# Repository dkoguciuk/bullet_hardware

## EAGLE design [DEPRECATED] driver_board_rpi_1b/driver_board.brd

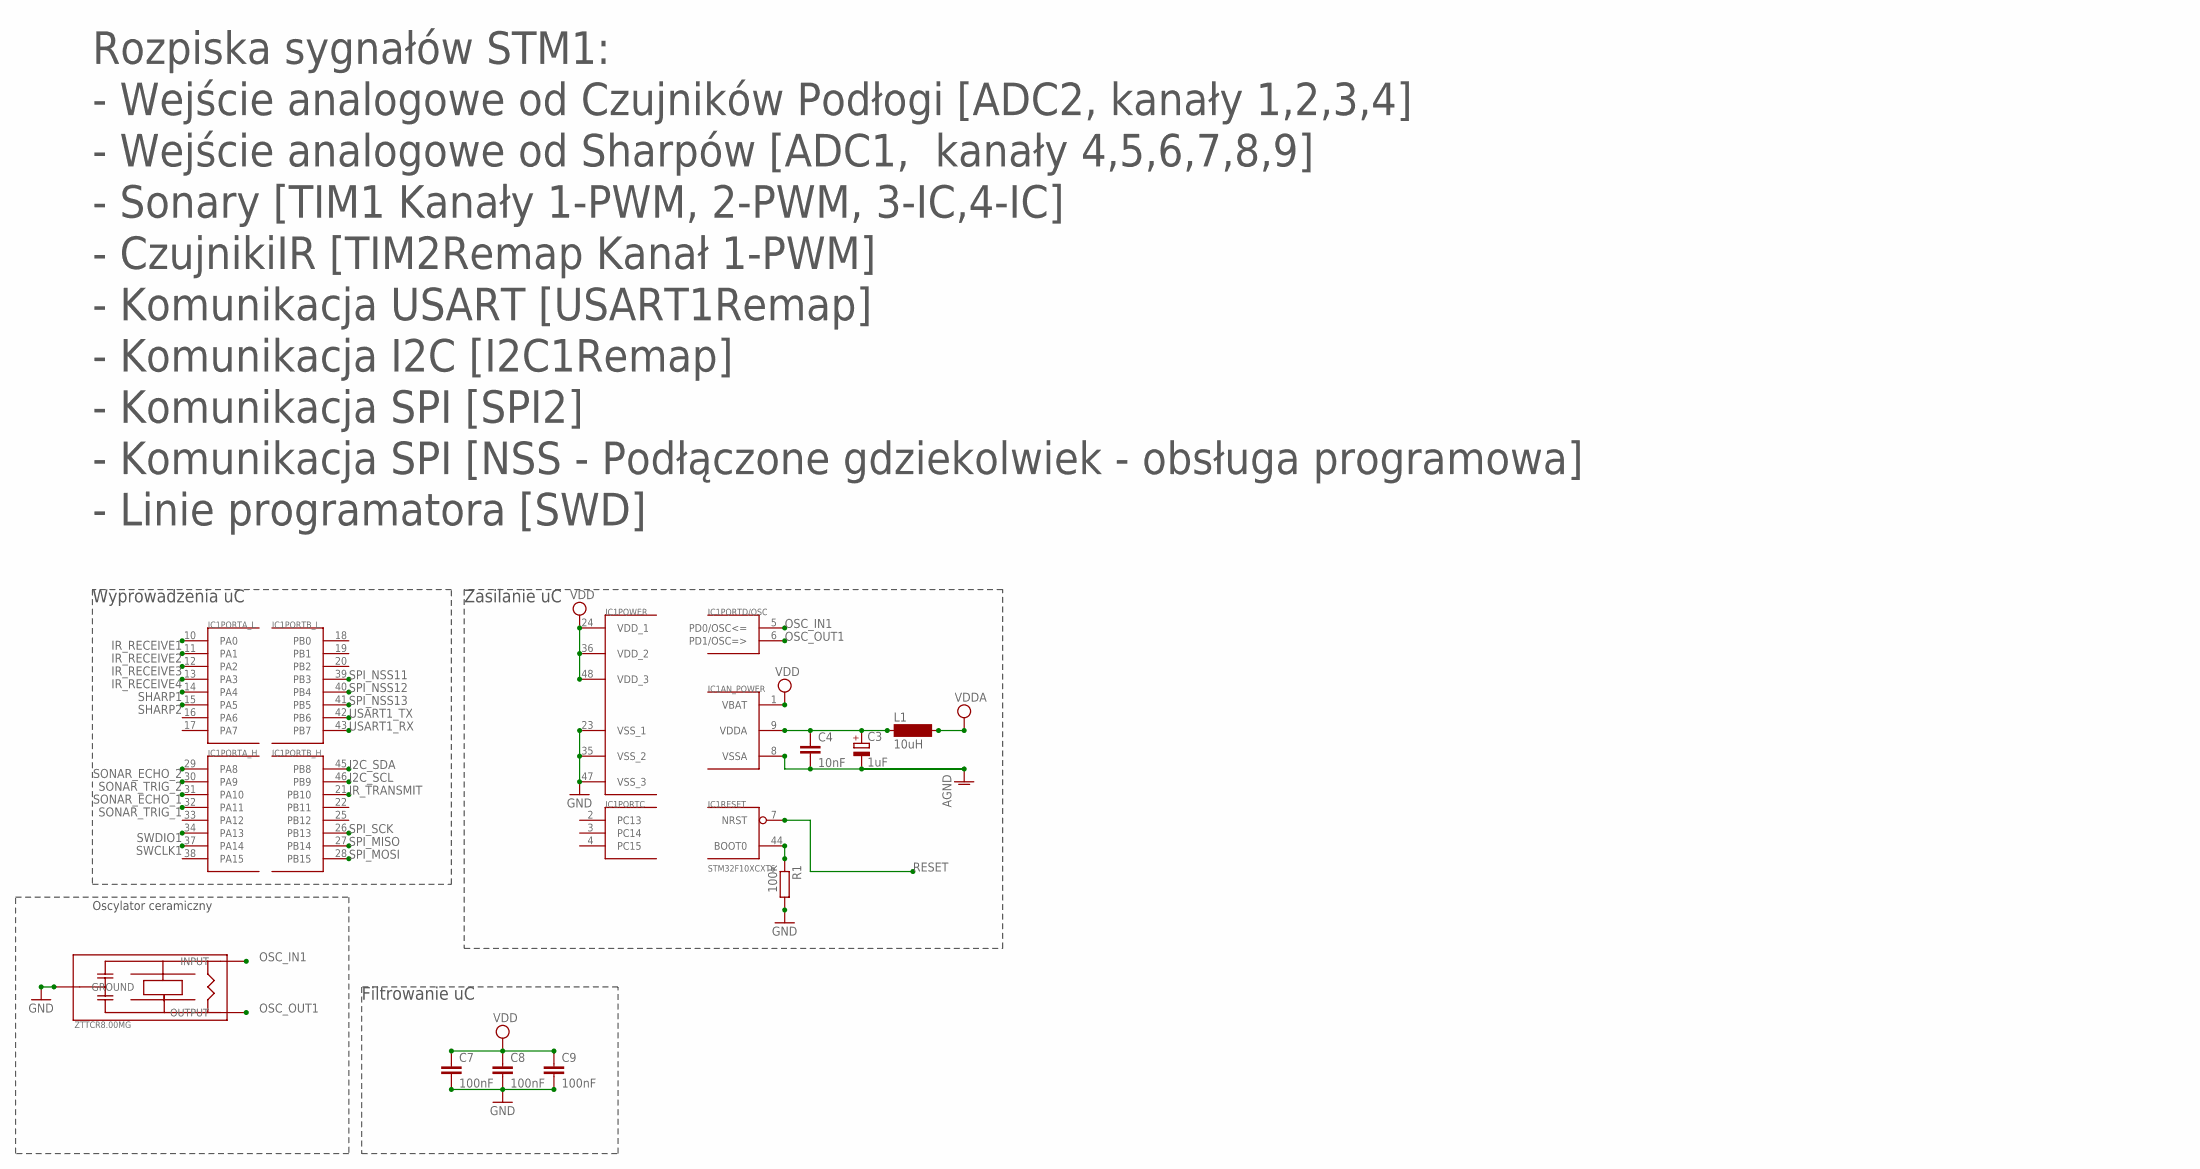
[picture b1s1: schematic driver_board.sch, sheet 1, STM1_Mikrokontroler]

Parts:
C3: 1uF; SMC_A
C4: 10nF; C0805
C7, C8, C9: 100nF; C0805
IC1: STM32F10XCXT6; TQFP48
L1: 10uH; SM-1206
R1: 100k; R0805
U$7: ZTTCR8.00MG

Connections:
AGND: C3.-, C4.2, IC1.8 (VSSA); also elsewhere on the board
GND: C7.2, C8.2, C9.2, IC1.23 (VSS_1), IC1.35 (VSS_2), IC1.47 (VSS_3), R1.2, U$7.GROUND; also elsewhere on the board
I2C_SCL: IC1.46 (PB9); also elsewhere on the board
I2C_SDA: IC1.45 (PB8); also elsewhere on the board
IR_RECEIVE1: IC1.10 (PA0); also elsewhere on the board
IR_RECEIVE2: IC1.11 (PA1); also elsewhere on the board
IR_RECEIVE3: IC1.12 (PA2); also elsewhere on the board
IR_RECEIVE4: IC1.13 (PA3); also elsewhere on the board
IR_TRANSMIT: IC1.21 (PB10); also elsewhere on the board
unnamed: IC1.44 (BOOT0), R1.1
unnamed: C3.+, C4.1, IC1.9 (VDDA), L1.1
OSC_IN1: IC1.5 (PD0/OSC<=), U$7.INPUT
OSC_OUT1: IC1.6 (PD1/OSC=>), U$7.OUTPUT
RESET: IC1.7 (NRST); also elsewhere on the board
SHARP1: IC1.14 (PA4); also elsewhere on the board
SHARP2: IC1.15 (PA5); also elsewhere on the board
SONAR_ECHO_1: IC1.31 (PA10); also elsewhere on the board
SONAR_ECHO_2: IC1.29 (PA8); also elsewhere on the board
SONAR_TRIG_1: IC1.32 (PA11); also elsewhere on the board
SONAR_TRIG_2: IC1.30 (PA9); also elsewhere on the board
SPI_MISO: IC1.27 (PB14); also elsewhere on the board
SPI_MOSI: IC1.28 (PB15); also elsewhere on the board
SPI_NSS11: IC1.39 (PB3); also elsewhere on the board
SPI_NSS12: IC1.40 (PB4); also elsewhere on the board
SPI_NSS13: IC1.41 (PB5); also elsewhere on the board
SPI_SCK: IC1.26 (PB13); also elsewhere on the board
SWCLK1: IC1.37 (PA14); also elsewhere on the board
SWDIO1: IC1.34 (PA13); also elsewhere on the board
USART1_RX: IC1.43 (PB7); also elsewhere on the board
USART1_TX: IC1.42 (PB6); also elsewhere on the board
VDD: C7.1, C8.1, C9.1, IC1.1 (VBAT), IC1.24 (VDD_1), IC1.36 (VDD_2), IC1.48 (VDD_3); also elsewhere on the board
VDDA: L1.2; also elsewhere on the board

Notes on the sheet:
Filtrowanie uC
Wyprowadzenia uC
Zasilanie uC
Oscylator ceramiczny
Rozpiska sygnałów STM1:
- Wejście analogowe od Sharpów [ADC1, kanały 4,5,6,7,8,9]
- Wejście analogowe od Czujników Podłogi [ADC2, kanały 1,2,3,4]
- Sonary [TIM1 Kanały 1-PWM, 2-PWM, 3-IC,4-IC]
- Komunikacja USART [USART1Remap]
- Komunikacja SPI [SPI2]
- Linie programatora [SWD]
- Komunikacja I2C [I2C1Remap]
- CzujnikiIR [TIM2Remap Kanał 1-PWM]
- Komunikacja SPI [NSS - Podłączone gdziekolwiek - obsługa programowa]

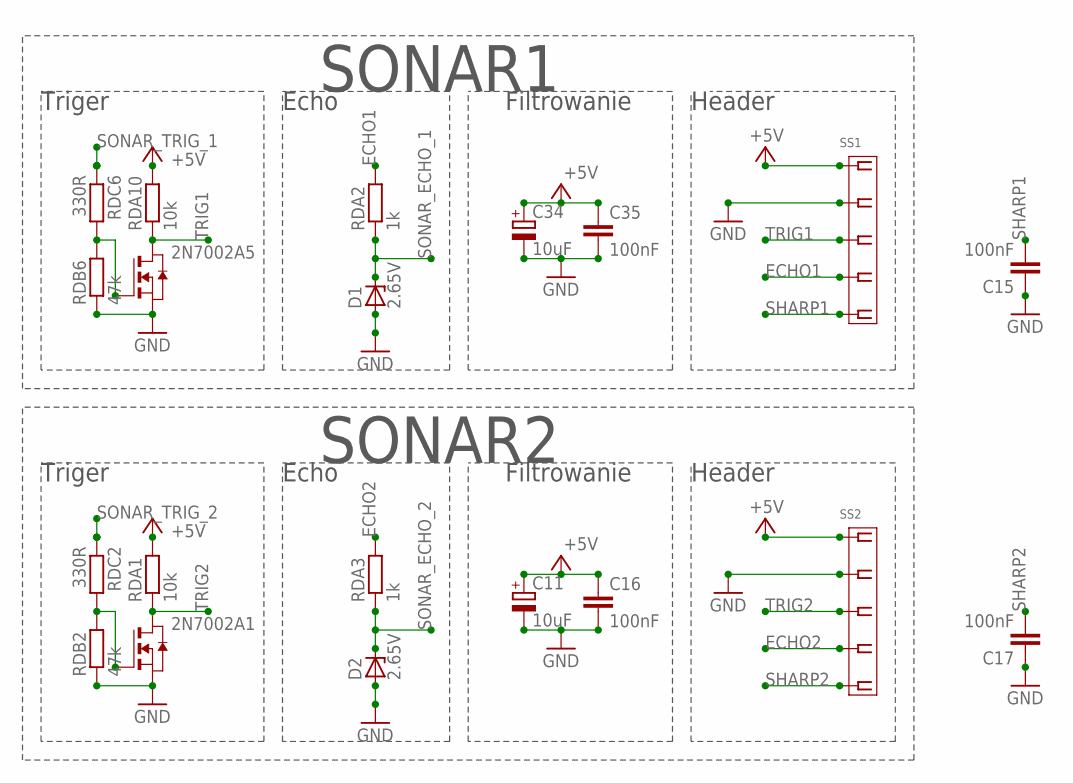
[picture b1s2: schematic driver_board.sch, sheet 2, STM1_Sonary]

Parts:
2N7002A1, 2N7002A5: NMOSSOT23; SOT-23
C11, C34: 10uF; SMC_A
C15, C16, C17, C35: 100nF; C0805
D1, D2: 2.65V; SOD80C
RDA1, RDA10: 10k; R0805
RDA2, RDA3: 1k; R0805
RDB2, RDB6: 47k; R0805
RDC2, RDC6: 330R; R0805
SS1, SS2: MOLEX-5268-05

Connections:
+5V: C11.+, C16.1, C34.+, C35.1, RDA1.2, RDA10.2, SS1.P$1 (1), SS2.P$1 (1); also elsewhere on the board
ECHO1: RDA2.2, SS1.P$4 (4)
ECHO2: RDA3.2, SS2.P$4 (4)
GND: 2N7002A1.2 (S), 2N7002A5.2 (S), C11.-, C15.1, C16.2, C17.1, C34.-, C35.2, D1.A, D2.A, RDB2.1, RDB6.1, SS1.P$2 (2), SS2.P$2 (2); also elsewhere on the board
unnamed: 2N7002A5.3 (G), RDB6.2, RDC6.2
unnamed: 2N7002A1.3 (G), RDB2.2, RDC2.2
SHARP1: C15.2, SS1.P$5 (5); also elsewhere on the board
SHARP2: C17.2, SS2.P$5 (5); also elsewhere on the board
SONAR_ECHO_1: D1.C, RDA2.1; also elsewhere on the board
SONAR_ECHO_2: D2.C, RDA3.1; also elsewhere on the board
SONAR_TRIG_1: RDC6.1; also elsewhere on the board
SONAR_TRIG_2: RDC2.1; also elsewhere on the board
TRIG1: 2N7002A5.1 (D), RDA10.1, SS1.P$3 (3)
TRIG2: 2N7002A1.1 (D), RDA1.1, SS2.P$3 (3)

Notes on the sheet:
Triger
Filtrowanie
Echo
SONAR1
Header
SONAR2

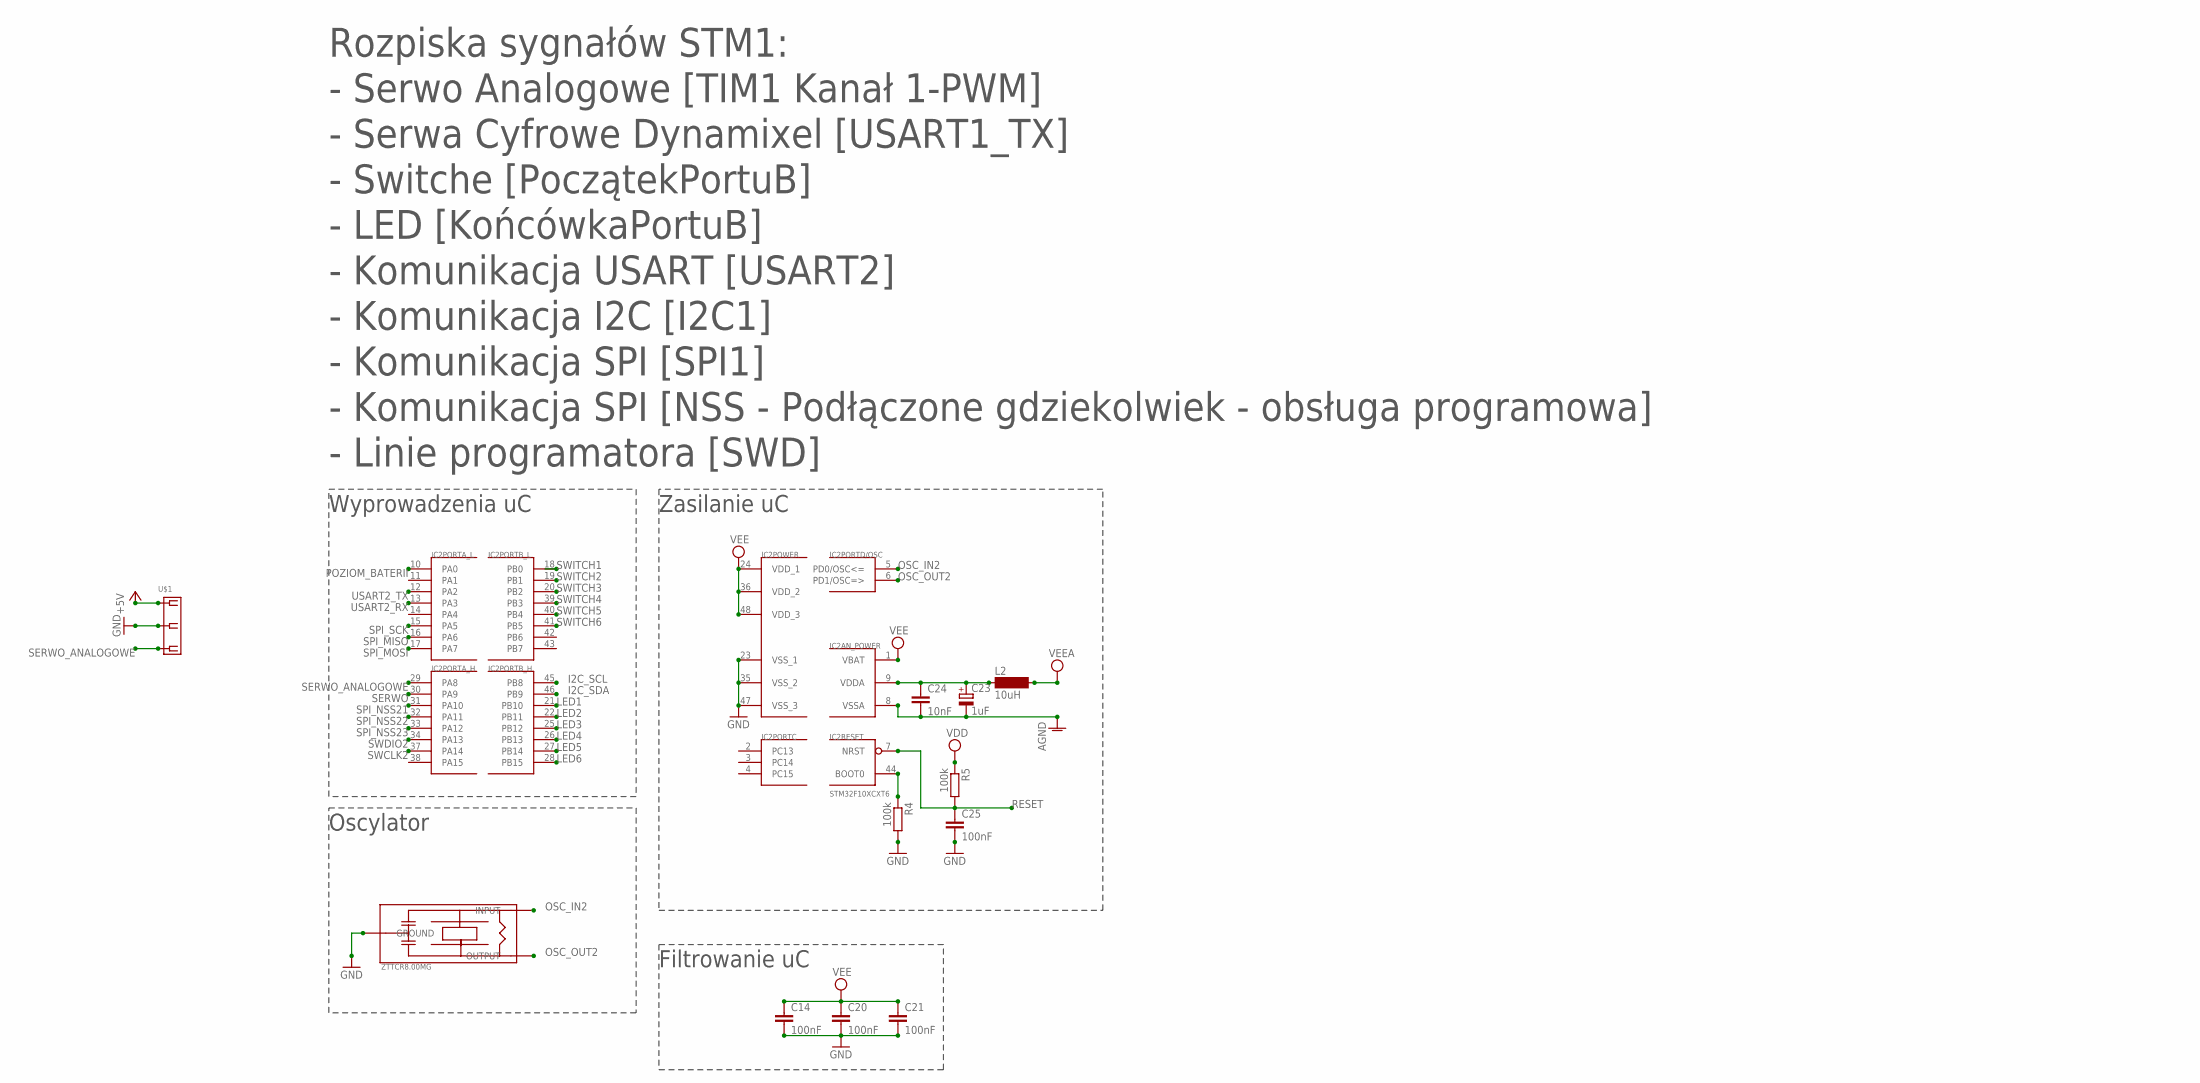
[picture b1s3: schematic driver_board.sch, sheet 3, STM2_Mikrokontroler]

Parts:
C14, C20, C21, C25: 100nF; C0805
C23: 1uF; SMC_A
C24: 10nF; C0805
IC2: STM32F10XCXT6; TQFP48
L2: 10uH; SM-1206
R4, R5: 100k; R0805
U$1: MOLEX-5268-03
U$8: ZTTCR8.00MG

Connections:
+5V: U$1.P$1 (1); also elsewhere on the board
AGND: C23.-, C24.2, IC2.8 (VSSA); also elsewhere on the board
GND: C14.2, C20.2, C21.2, C25.2, IC2.23 (VSS_1), IC2.35 (VSS_2), IC2.47 (VSS_3), R4.2, U$1.P$2 (2), U$8.GROUND; also elsewhere on the board
I2C_SCL: IC2.45 (PB8); also elsewhere on the board
I2C_SDA: IC2.46 (PB9); also elsewhere on the board
LED1: IC2.21 (PB10); also elsewhere on the board
LED2: IC2.22 (PB11); also elsewhere on the board
LED3: IC2.25 (PB12); also elsewhere on the board
LED4: IC2.26 (PB13); also elsewhere on the board
LED5: IC2.27 (PB14); also elsewhere on the board
LED6: IC2.28 (PB15); also elsewhere on the board
unnamed: C23.+, C24.1, IC2.9 (VDDA), L2.1
unnamed: IC2.44 (BOOT0), R4.1
OSC_IN2: IC2.5 (PD0/OSC<=), U$8.INPUT
OSC_OUT2: IC2.6 (PD1/OSC=>), U$8.OUTPUT
POZIOM_BATERII: IC2.10 (PA0); also elsewhere on the board
RESET: C25.1, IC2.7 (NRST), R5.2; also elsewhere on the board
SERWO: IC2.30 (PA9); also elsewhere on the board
SERWO_ANALOGOWE: IC2.29 (PA8), U$1.P$3 (3)
SPI_MISO: IC2.16 (PA6); also elsewhere on the board
SPI_MOSI: IC2.17 (PA7); also elsewhere on the board
SPI_NSS21: IC2.31 (PA10); also elsewhere on the board
SPI_NSS22: IC2.32 (PA11); also elsewhere on the board
SPI_NSS23: IC2.33 (PA12); also elsewhere on the board
SPI_SCK: IC2.15 (PA5); also elsewhere on the board
SWCLK2: IC2.37 (PA14); also elsewhere on the board
SWDIO2: IC2.34 (PA13); also elsewhere on the board
SWITCH1: IC2.18 (PB0); also elsewhere on the board
SWITCH2: IC2.19 (PB1); also elsewhere on the board
SWITCH3: IC2.20 (PB2); also elsewhere on the board
SWITCH4: IC2.39 (PB3); also elsewhere on the board
SWITCH5: IC2.40 (PB4); also elsewhere on the board
SWITCH6: IC2.41 (PB5); also elsewhere on the board
USART2_RX: IC2.13 (PA3); also elsewhere on the board
USART2_TX: IC2.12 (PA2); also elsewhere on the board
VDD: R5.1; also elsewhere on the board
VEE: C14.1, C20.1, C21.1, IC2.1 (VBAT), IC2.24 (VDD_1), IC2.36 (VDD_2), IC2.48 (VDD_3); also elsewhere on the board
VEEA: L2.2; also elsewhere on the board

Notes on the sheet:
Wyprowadzenia uC
Zasilanie uC
Oscylator
Filtrowanie uC
Rozpiska sygnałów STM1:
- Komunikacja USART [USART2]
- Komunikacja SPI [SPI1]
- Komunikacja SPI [NSS - Podłączone gdziekolwiek - obsługa programowa]
- Serwa Cyfrowe Dynamixel [USART1_TX]
- Serwo Analogowe [TIM1 Kanał 1-PWM]
- Komunikacja I2C [I2C1]
- Switche [PoczątekPortuB]
- LED [KońcówkaPortuB]
- Linie programatora [SWD]

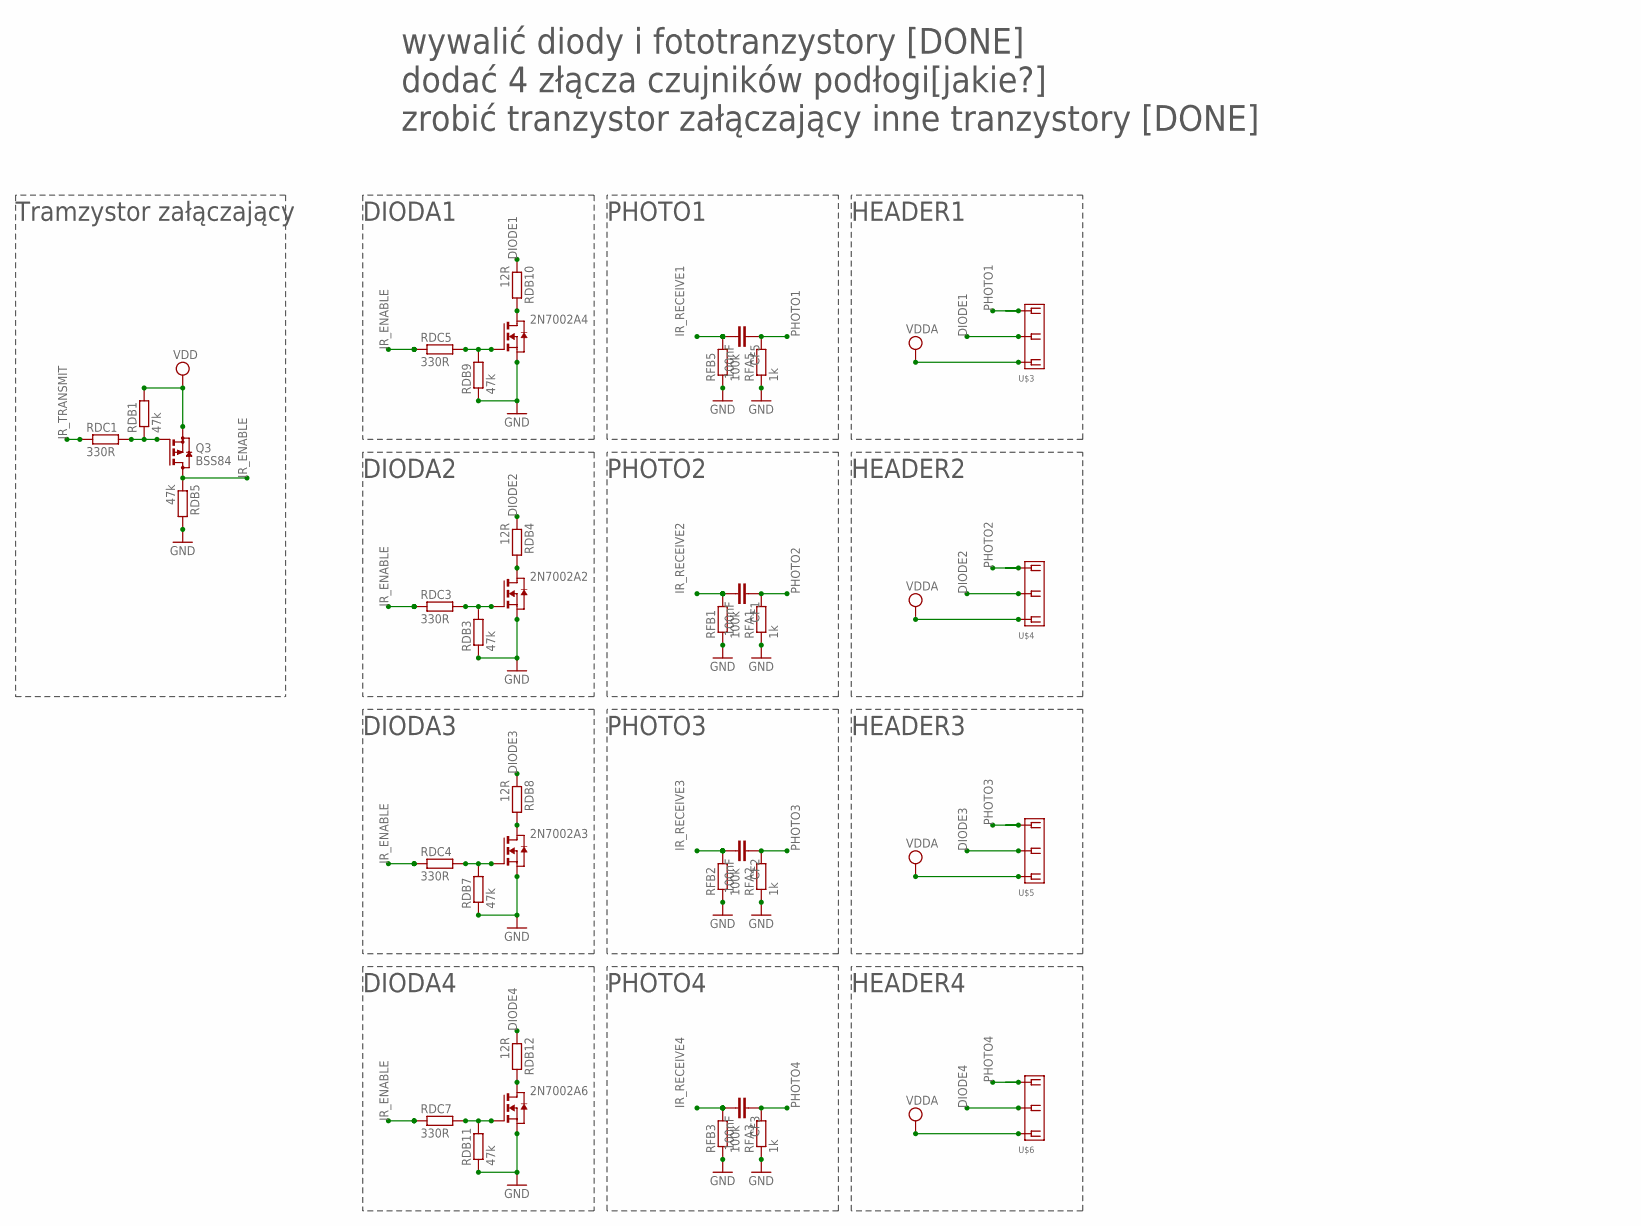
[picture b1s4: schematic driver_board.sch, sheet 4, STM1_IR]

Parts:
2N7002A2, 2N7002A3, 2N7002A4, 2N7002A6: NMOSSOT23; SOT-23
CF1, CF2, CF3, CF5: 100nF; C0805
Q3: BSS84; SOT23
RDB1, RDB3, RDB5, RDB7, RDB9, RDB11: 47k; R0805
RDB4, RDB8, RDB10, RDB12: 12R; R0805
RDC1, RDC3, RDC4, RDC5, RDC7: 330R; R0805
RFA1, RFA2, RFA3, RFA5: 1k; R0805
RFB1, RFB2, RFB3, RFB5: 100k; R0805
U$3, U$4, U$5, U$6: MOLEX-5268-03

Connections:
DIODE1: RDB10.1, U$3.P$2 (2)
DIODE2: RDB4.1, U$4.P$2 (2)
DIODE3: RDB8.1, U$5.P$2 (2)
DIODE4: RDB12.1, U$6.P$2 (2)
GND: 2N7002A2.2 (S), 2N7002A3.2 (S), 2N7002A4.2 (S), 2N7002A6.2 (S), RDB3.1, RDB5.2, RDB7.1, RDB9.1, RDB11.1, RFA1.1, RFA2.1, RFA3.1, RFA5.1, RFB1.1, RFB2.1, RFB3.1, RFB5.1; also elsewhere on the board
IR_ENABLE: Q3.3 (D), RDB5.1, RDC3.1, RDC4.1, RDC5.1, RDC7.1
IR_RECEIVE1: CF5.2, RFB5.2; also elsewhere on the board
IR_RECEIVE2: CF1.2, RFB1.2; also elsewhere on the board
IR_RECEIVE3: CF2.2, RFB2.2; also elsewhere on the board
IR_RECEIVE4: CF3.2, RFB3.2; also elsewhere on the board
IR_TRANSMIT: RDC1.1; also elsewhere on the board
unnamed: Q3.1 (G), RDB1.1, RDC1.2
unnamed: 2N7002A2.3 (G), RDB3.2, RDC3.2
unnamed: 2N7002A2.1 (D), RDB4.2
unnamed: 2N7002A3.3 (G), RDB7.2, RDC4.2
unnamed: 2N7002A3.1 (D), RDB8.2
unnamed: 2N7002A4.3 (G), RDB9.2, RDC5.2
unnamed: 2N7002A4.1 (D), RDB10.2
unnamed: 2N7002A6.3 (G), RDB11.2, RDC7.2
unnamed: 2N7002A6.1 (D), RDB12.2
PHOTO1: CF5.1, RFA5.2, U$3.P$3 (3)
PHOTO2: CF1.1, RFA1.2, U$4.P$3 (3)
PHOTO3: CF2.1, RFA2.2, U$5.P$3 (3)
PHOTO4: CF3.1, RFA3.2, U$6.P$3 (3)
VDD: Q3.2 (S), RDB1.2, U$3.P$1 (1), U$4.P$1 (1), U$5.P$1 (1), U$6.P$1 (1); also elsewhere on the board

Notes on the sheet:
zrobić tranzystor załączający inne tranzystory [DONE]
dodać 4 złącza czujników podłogi[jakie?]
wywalić diody i fototranzystory [DONE]
Tramzystor załączający
DIODA1
PHOTO1
HEADER1
DIODA2
PHOTO2
HEADER2
DIODA3
PHOTO3
HEADER3
DIODA4
PHOTO4
HEADER4

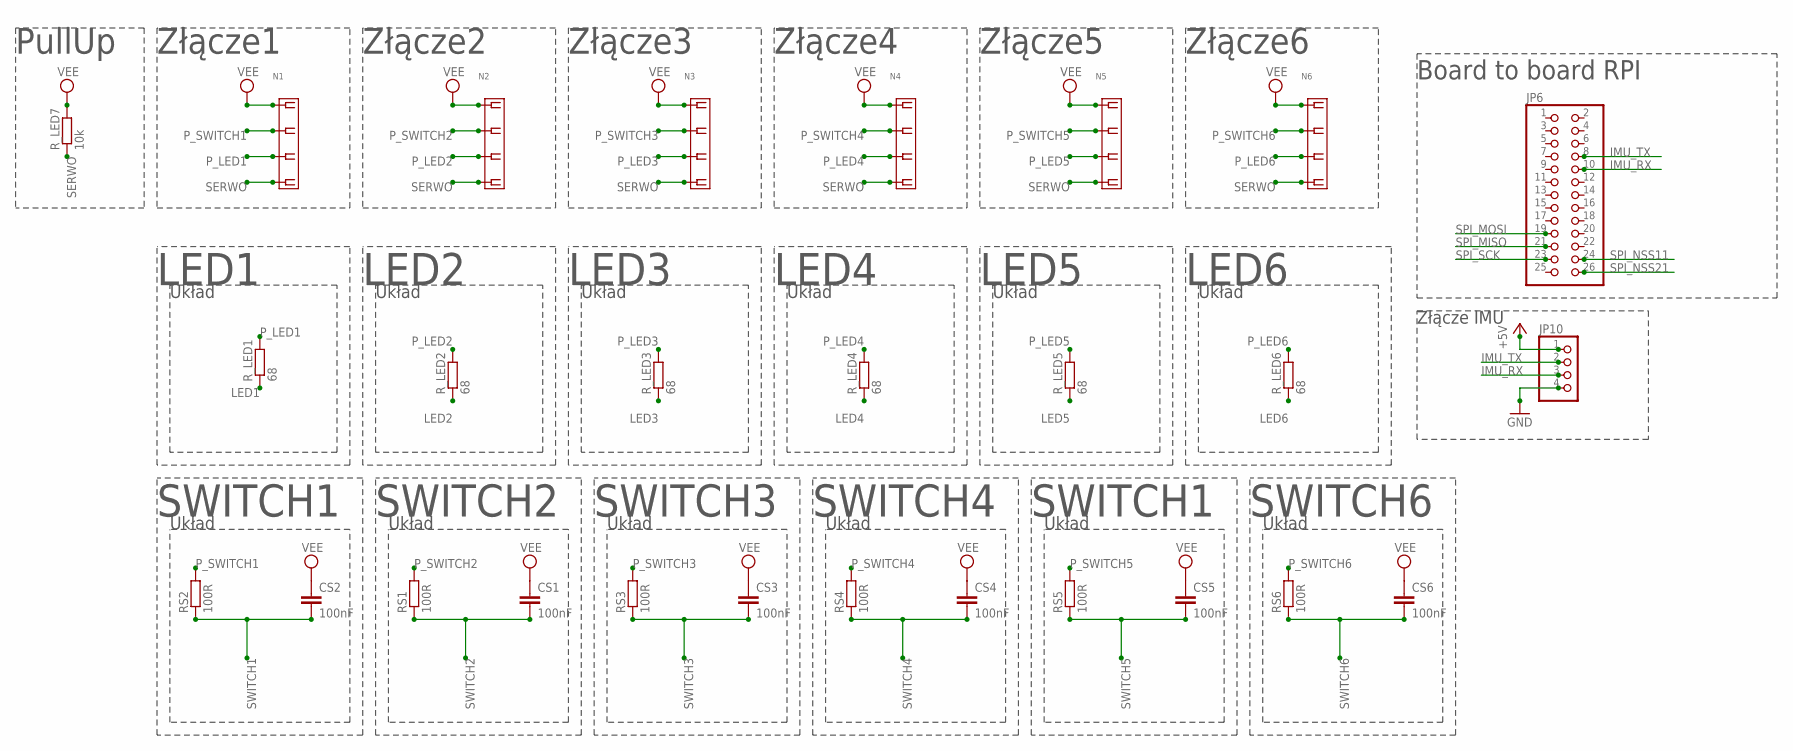
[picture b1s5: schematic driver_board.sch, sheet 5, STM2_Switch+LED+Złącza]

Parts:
CS1, CS2, CS3, CS4, CS5, CS6: 100nF; C0805
JP6: PINHD-2X13; 2X13
JP10: PINHD-1X4; 1X04
N1, N2, N3, N4, N5, N6: MOLEX-5268-04
RS1, RS2, RS3, RS4, RS5, RS6: 100R; R0805
R_LED1, R_LED2, R_LED3, R_LED4, R_LED5, R_LED6: 68; R0805
R_LED7: 10k; R1206

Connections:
+5V: JP10.1; also elsewhere on the board
GND: JP10.4; also elsewhere on the board
IMU_RX: JP6.10, JP10.3
IMU_TX: JP6.8, JP10.2
LED1: R_LED1.1; also elsewhere on the board
LED2: R_LED2.1; also elsewhere on the board
LED3: R_LED3.1; also elsewhere on the board
LED4: R_LED4.1; also elsewhere on the board
LED5: R_LED5.1; also elsewhere on the board
LED6: R_LED6.1; also elsewhere on the board
P_LED1: N1.P$3 (3), R_LED1.2
P_LED2: N2.P$3 (3), R_LED2.2
P_LED3: N3.P$3 (3), R_LED3.2
P_LED4: N4.P$3 (3), R_LED4.2
P_LED5: N5.P$3 (3), R_LED5.2
P_LED6: N6.P$3 (3), R_LED6.2
P_SWITCH1: N1.P$2 (2), RS2.2
P_SWITCH2: N2.P$2 (2), RS1.2
P_SWITCH3: N3.P$2 (2), RS3.2
P_SWITCH4: N4.P$2 (2), RS4.2
P_SWITCH5: N5.P$2 (2), RS5.2
P_SWITCH6: N6.P$2 (2), RS6.2
SERWO: N1.P$4 (4), N2.P$4 (4), N3.P$4 (4), N4.P$4 (4), N5.P$4 (4), N6.P$4 (4), R_LED7.1; also elsewhere on the board
SPI_MISO: JP6.21; also elsewhere on the board
SPI_MOSI: JP6.19; also elsewhere on the board
SPI_NSS11: JP6.24; also elsewhere on the board
SPI_NSS21: JP6.26; also elsewhere on the board
SPI_SCK: JP6.23; also elsewhere on the board
SWITCH1: CS2.2, RS2.1; also elsewhere on the board
SWITCH2: CS1.2, RS1.1; also elsewhere on the board
SWITCH3: CS3.2, RS3.1; also elsewhere on the board
SWITCH4: CS4.2, RS4.1; also elsewhere on the board
SWITCH5: CS5.2, RS5.1; also elsewhere on the board
SWITCH6: CS6.2, RS6.1; also elsewhere on the board
VEE: CS1.1, CS2.1, CS3.1, CS4.1, CS5.1, CS6.1, N1.P$1 (1), N2.P$1 (1), N3.P$1 (1), N4.P$1 (1), N5.P$1 (1), N6.P$1 (1), R_LED7.2; also elsewhere on the board

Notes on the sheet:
Układ
SWITCH1
LED1
LED2
LED3
LED4
LED5
LED6
Złącze1
SWITCH2
SWITCH3
SWITCH4
SWITCH6
PullUp
Board to board RPI
Złącze IMU
Złącze2
Złącze3
Złącze4
Złącze5
Złącze6

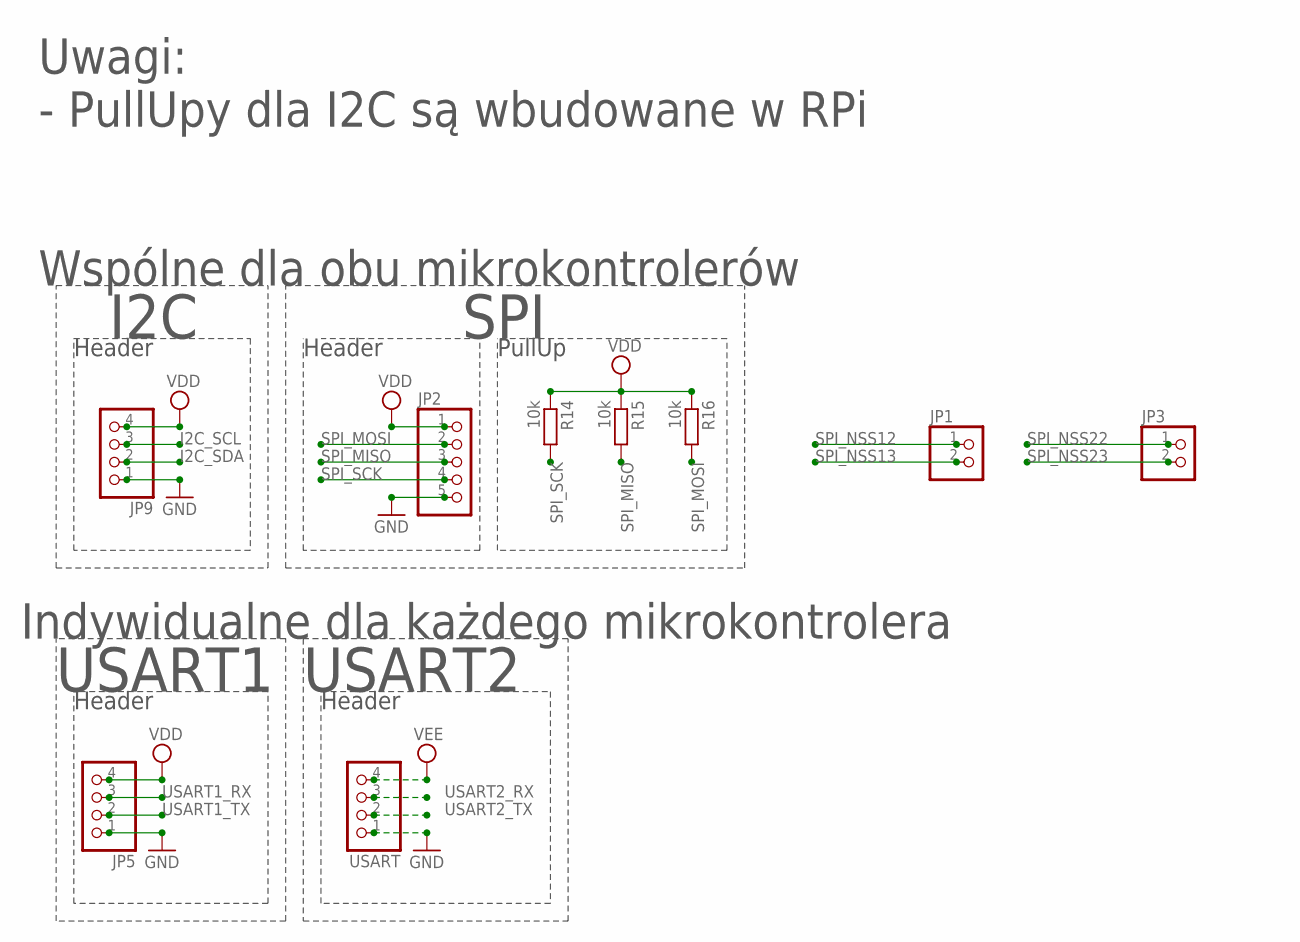
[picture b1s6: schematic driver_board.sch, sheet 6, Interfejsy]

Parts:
JP1, JP3: PINHD-1X2; 1X02
JP2: PINHD-1X5; 1X05
JP5, JP9: PINHD-1X4; 1X04
R14, R15, R16: 10k; R0805
USART: PINHD-1X4; 1X04

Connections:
GND: JP2.5, JP5.1, JP9.1, USART.1; also elsewhere on the board
I2C_SCL: JP9.3; also elsewhere on the board
I2C_SDA: JP9.2; also elsewhere on the board
SPI_MISO: JP2.3, R15.2; also elsewhere on the board
SPI_MOSI: JP2.2, R16.2; also elsewhere on the board
SPI_NSS12: JP1.1; also elsewhere on the board
SPI_NSS13: JP1.2; also elsewhere on the board
SPI_NSS22: JP3.1; also elsewhere on the board
SPI_NSS23: JP3.2; also elsewhere on the board
SPI_SCK: JP2.4, R14.2; also elsewhere on the board
USART1_RX: JP5.3; also elsewhere on the board
USART1_TX: JP5.2; also elsewhere on the board
USART2_RX: USART.3; also elsewhere on the board
USART2_TX: USART.2; also elsewhere on the board
VDD: JP2.1, JP5.4, JP9.4, R14.1, R15.1, R16.1; also elsewhere on the board
VEE: USART.4; also elsewhere on the board

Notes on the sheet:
Header
PullUp
I2C
SPI
USART1
Indywidualne dla każdego mikrokontrolera
Wspólne dla obu mikrokontrolerów
USART2
Uwagi:
- PullUpy dla I2C są wbudowane w RPi

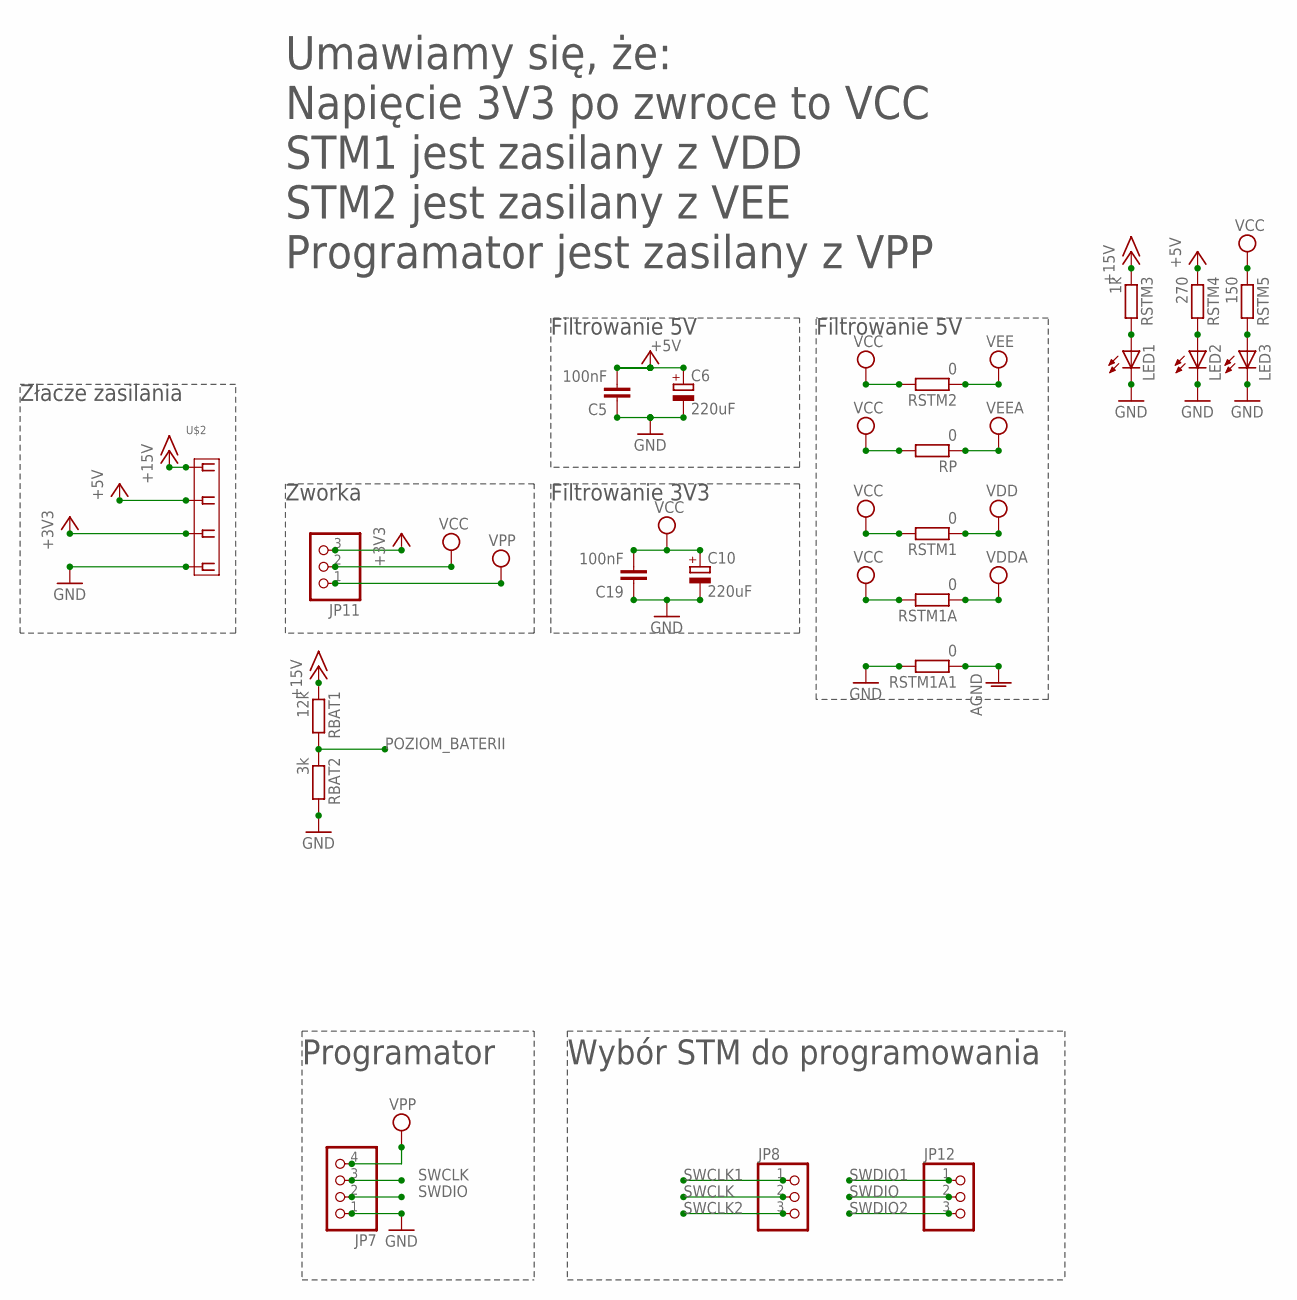
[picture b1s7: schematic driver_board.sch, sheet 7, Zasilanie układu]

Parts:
C5, C19: 100nF; C0805
C6, C10: 220uF; SMC_A
JP7: PINHD-1X4; 1X04
JP8, JP11, JP12: PINHD-1X3; 1X03
LED1, LED2, LED3: LEDCHIPLED_0805; CHIPLED_0805
RBAT1: 12k; R0805
RBAT2: 3k; R0805
RP: 0; R0805
RSTM1, RSTM1A, RSTM1A1, RSTM2: 0; R0805
RSTM3: 1k; R0805
RSTM4: 270; R0805
RSTM5: 150; R0805
U$2: MOLEX-5268-04

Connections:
+3V3: JP11.3, U$2.P$3 (3)
+5V: C5.2, C6.+, RSTM4.1, U$2.P$2 (2); also elsewhere on the board
+15V: RBAT1.1, RSTM3.1, U$2.P$1 (1)
AGND: RSTM1A1.1; also elsewhere on the board
GND: C5.1, C6.-, C10.-, C19.1, JP7.1, LED1.C, LED2.C, LED3.C, RBAT2.2, RSTM1A1.2, U$2.P$4 (4); also elsewhere on the board
unnamed: LED2.A, RSTM4.2
unnamed: LED3.A, RSTM5.2
unnamed: LED1.A, RSTM3.2
POZIOM_BATERII: RBAT1.2, RBAT2.1; also elsewhere on the board
SWCLK: JP7.3, JP8.2
SWCLK1: JP8.1; also elsewhere on the board
SWCLK2: JP8.3; also elsewhere on the board
SWDIO: JP7.2, JP12.2
SWDIO1: JP12.1; also elsewhere on the board
SWDIO2: JP12.3; also elsewhere on the board
VCC: C10.+, C19.2, JP11.2, RP.2, RSTM1.2, RSTM1A.2, RSTM2.2, RSTM5.1
VDD: RSTM1.1; also elsewhere on the board
VDDA: RSTM1A.1; also elsewhere on the board
VEE: RSTM2.1; also elsewhere on the board
VEEA: RP.1; also elsewhere on the board
VPP: JP7.4, JP11.1

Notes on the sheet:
Zworka
STM1 jest zasilany z VDD
STM2 jest zasilany z VEE
Umawiamy się, że:
Programator jest zasilany z VPP
Napięcie 3V3 po zwroce to VCC
Filtrowanie 5V
Filtrowanie 3V3
Programator
Wybór STM do programowania
Złacze zasilania

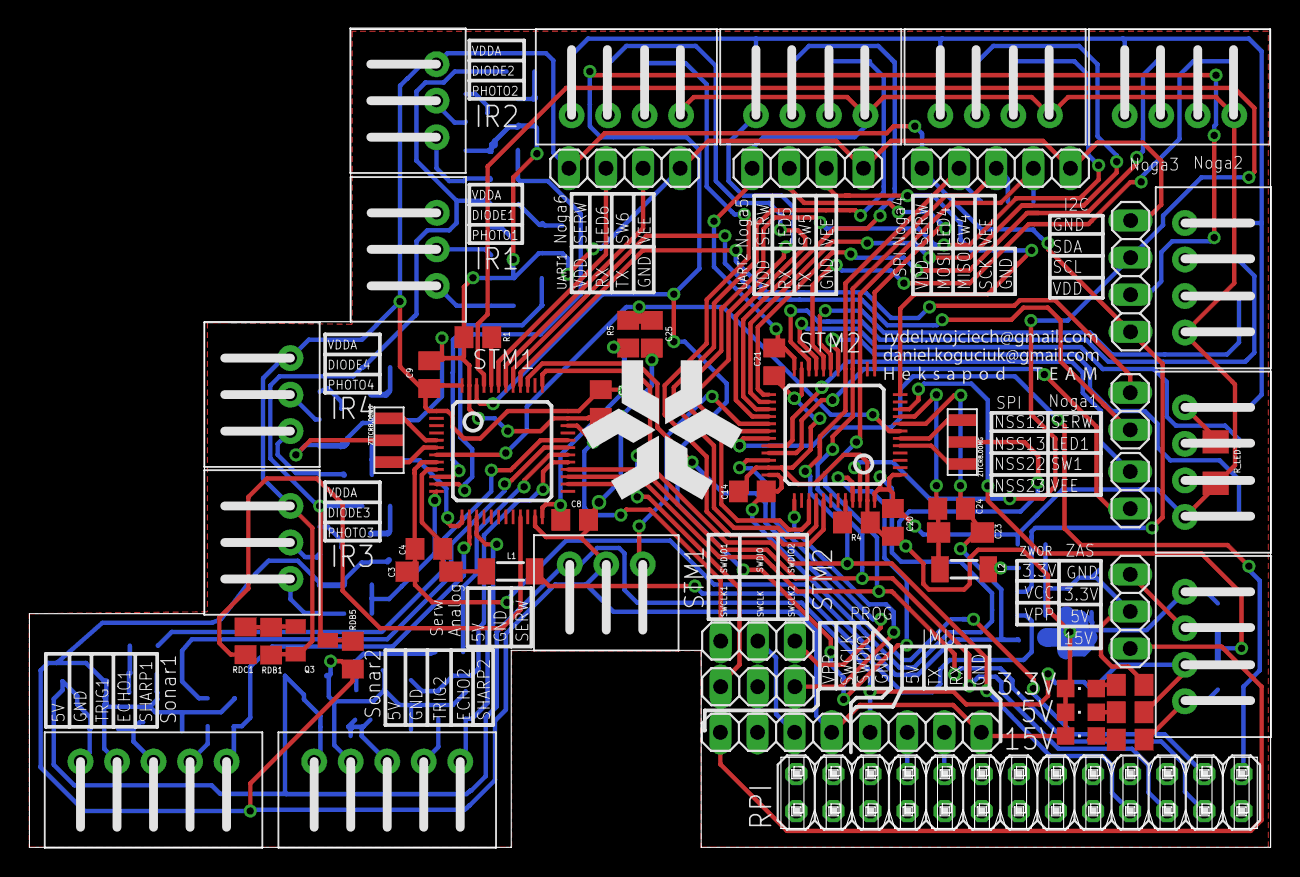
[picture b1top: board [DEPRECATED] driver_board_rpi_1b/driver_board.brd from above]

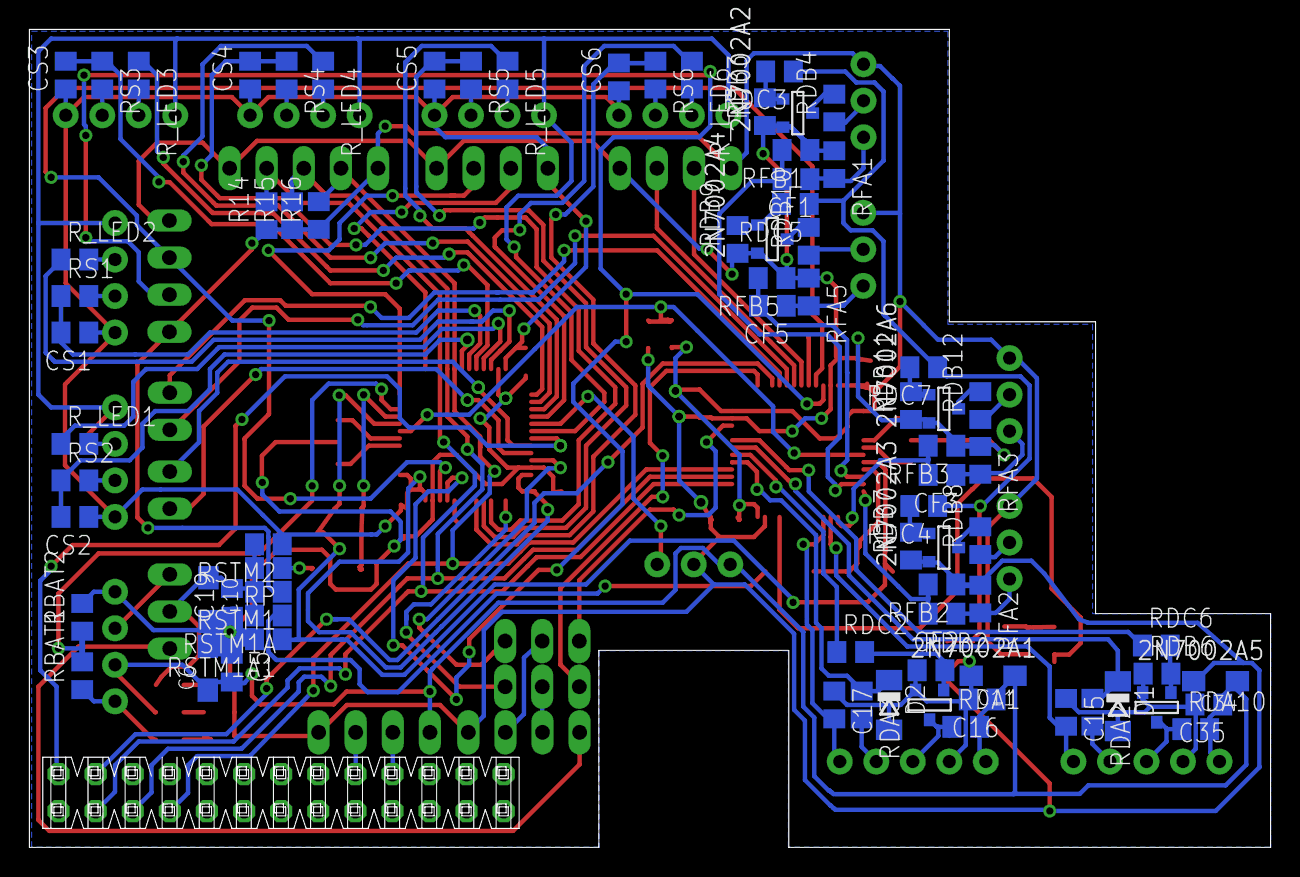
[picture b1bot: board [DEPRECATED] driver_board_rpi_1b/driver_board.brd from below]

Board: 2 copper layers, 85.0 x 56.0 mm, 135 parts (78 on the bottom side), 108 nets.
